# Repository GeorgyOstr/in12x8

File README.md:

# Yet another nixie display RTC project.

### Overview
Wanted to desing esp32 powered control board usable for multiple different 8 tubes clock.
Want to make 3 iterations of clocks.

Will try to code in platformio.

Case: glass lid, 3d print support, metal exterior.
Single Type-C connector.

Based on Tom Titor design.

### Target for v1
PCB design in EAGLE. Fusion for case.
All caps MLCC.

1. Display board 
    * 2 layers
    * Minimal footprint
    * SMD only
    * Circuitry on one side (tubes on opposite)
    * HV path minimized
    * 8 tubes IN12
    * [HV552](https://ww1.microchip.com/downloads/en/DeviceDoc/HV5523-32-Channel-Serial-to-Parallel-Converter-with-Open-Drain-Outputs-Data-Sheet-20005700A.pdf)
    
    * optional: custom HV supply onboard
    
2. Control board (beta)
    * 2 layers
    * Modules usage
    * Same footprint as display
    * Circuitry on one side
    * ESP32
    * [DS3232](https://www.analog.com/media/en/technical-documentation/data-sheets/ds3232.pdf)
    * [Taylor Electronics HVPS 1364](https://www.shop-tes.com/content/Datasheets/8002K.pdf)
    * [Potentiometer](https://www.mouser.jp/datasheet/2/609/MAX5460_MAX5468-3129691.pdf)
    * [Type C](https://www.mouser.jp/ProductDetail/Wurth-Elektronik/632723300021?qs=t3bE0qb%2FqEJYzZ4bEQN6Ug%3D%3D)
    * Full control on HV 

    * optional: battery support

### Target for v2

2. Control board
    * 2 layers
    * Minimal footprint
    * SMD only except USB-c
    * No modules
    * Battery support

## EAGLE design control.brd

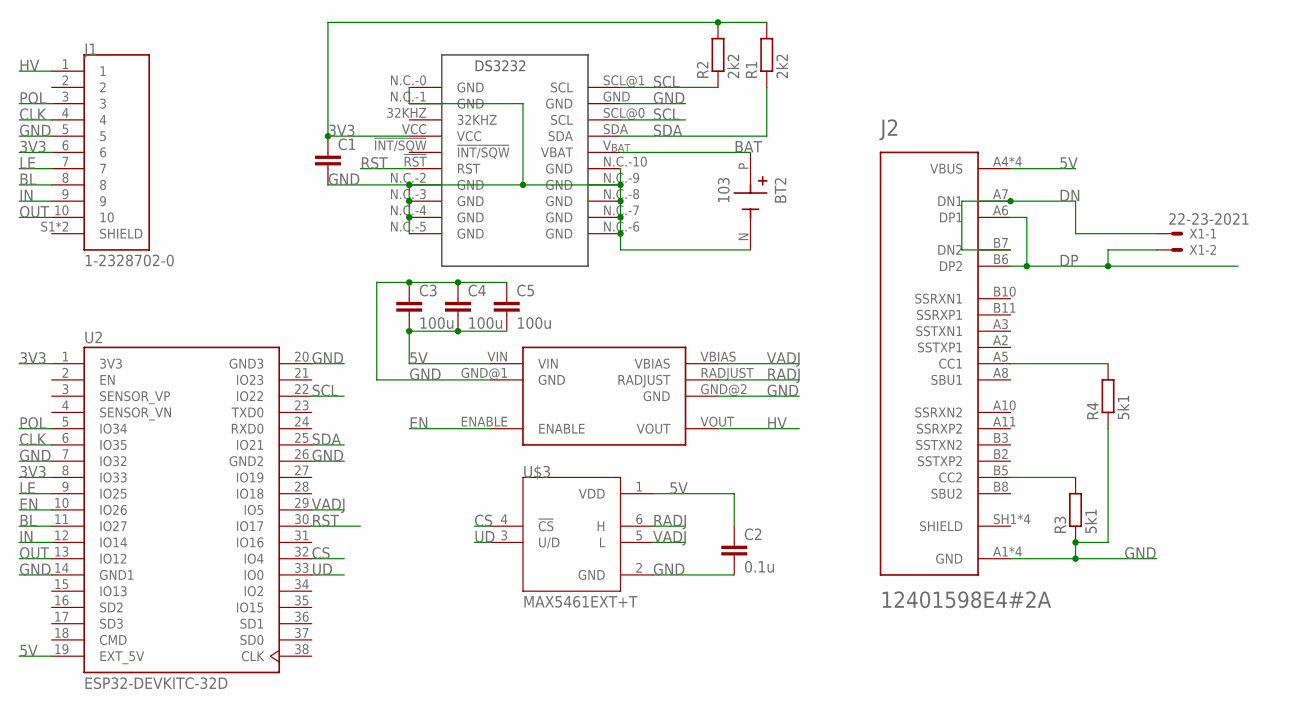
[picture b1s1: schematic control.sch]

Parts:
BT2: 103; BAT_103
C1: C-EUC0805; C0805
C2: 0.1u; C0805
C3, C4, C5: 100u; C1210
J1: 1-2328702-0; TE_1-2328702-0
J2: 12401598E4#2A; AMPHENOL_12401598E4#2A
R1, R2: 2k2; R0805
R3, R4: 5k1; R0805
U2: ESP32-DEVKITC-32D; MODULE_ESP32-DEVKITC-32D
U$1: DS3232; SO20-2
U$2: HV_PSU
U$3: MAX5461EXT+T; SOT65P210X110-6N
X1: 22-23-2021

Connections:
3V3: C1.1, J1.6, R1.2, R2.2, U2.1 (3V3), U2.8 (IO33), U$1.VCC
5V: C2.1, C3.2, C4.2, C5.2, J2.A4 (VBUS), J2.A9 (VBUS), J2.B4 (VBUS), J2.B9 (VBUS), U2.19 (EXT_5V), U$2.VIN, U$3.1 (VDD)
BAT: BT2.P (POS), U$1.V_{BAT} (VBAT)
BL: J1.8, U2.11 (IO27)
CLK: J1.4, U2.6 (IO35)
CS: U2.32 (IO4), U$3.4 (!CS)
DN: J2.A7 (DN1), J2.B7 (DN2), X1.1
DP: J2.A6 (DP1), J2.B6 (DP2), X1.2
EN: U2.10 (IO26), U$2.ENABLE
GND: BT2.N (NEG), C1.2, C2.2, C3.1, C4.1, C5.1, J1.5, J2.A1 (GND), J2.A12 (GND), J2.B1 (GND), J2.B12 (GND), R3.1, R4.1, U2.7 (IO32), U2.14 (GND1), U2.20 (GND3), U2.26 (GND2), U$1.GND, U$1.N.C.-0 (GND), U$1.N.C.-1 (GND), U$1.N.C.-2 (GND), U$1.N.C.-3 (GND), U$1.N.C.-4 (GND), U$1.N.C.-5 (GND), U$1.N.C.-6 (GND), U$1.N.C.-7 (GND), U$1.N.C.-8 (GND), U$1.N.C.-9 (GND), U$1.N.C.-10 (GND), U$2.GND@1 (GND), U$2.GND@2 (GND), U$3.2 (GND)
HV: J1.1, U$2.VOUT
IN: J1.9, U2.12 (IO14)
LE: J1.7, U2.9 (IO25)
unnamed: J2.B5 (CC2), R3.2
unnamed: J2.A5 (CC1), R4.2
OUT: J1.10, U2.13 (IO12)
POL: J1.3, U2.5 (IO34)
RADJ: U$2.RADJUST, U$3.6 (H)
RST: U2.30 (IO17), U$1.!RST (RST)
SCL: R2.1, U2.22 (IO22), U$1.SCL@0 (SCL), U$1.SCL@1 (SCL)
SDA: R1.1, U2.25 (IO21), U$1.SDA
SHIELD: J2.SH1 (SHIELD), J2.SH2 (SHIELD), J2.SH3 (SHIELD), J2.SH4 (SHIELD)
UD: U2.33 (IO0), U$3.3 (U/D)
VADJ: U2.29 (IO5), U$2.VBIAS, U$3.5 (L)

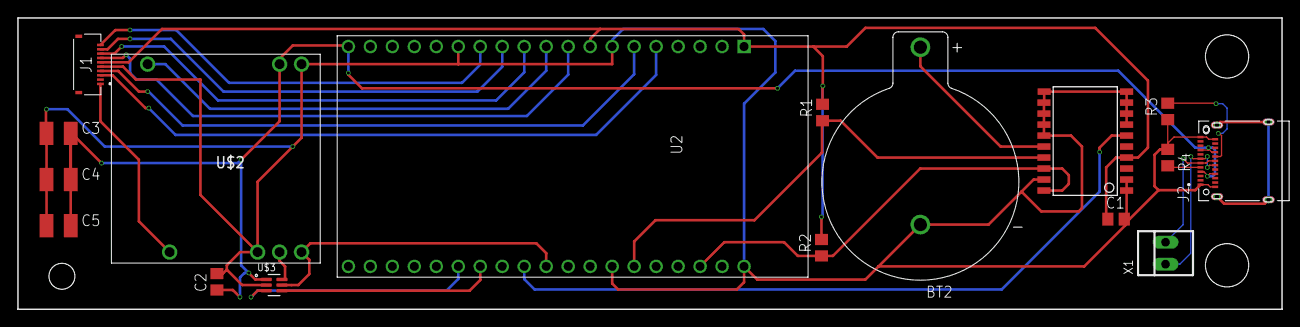
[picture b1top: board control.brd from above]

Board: 2 copper layers, 146.1 x 33.7 mm, 17 parts (0 on the bottom side), 24 nets.

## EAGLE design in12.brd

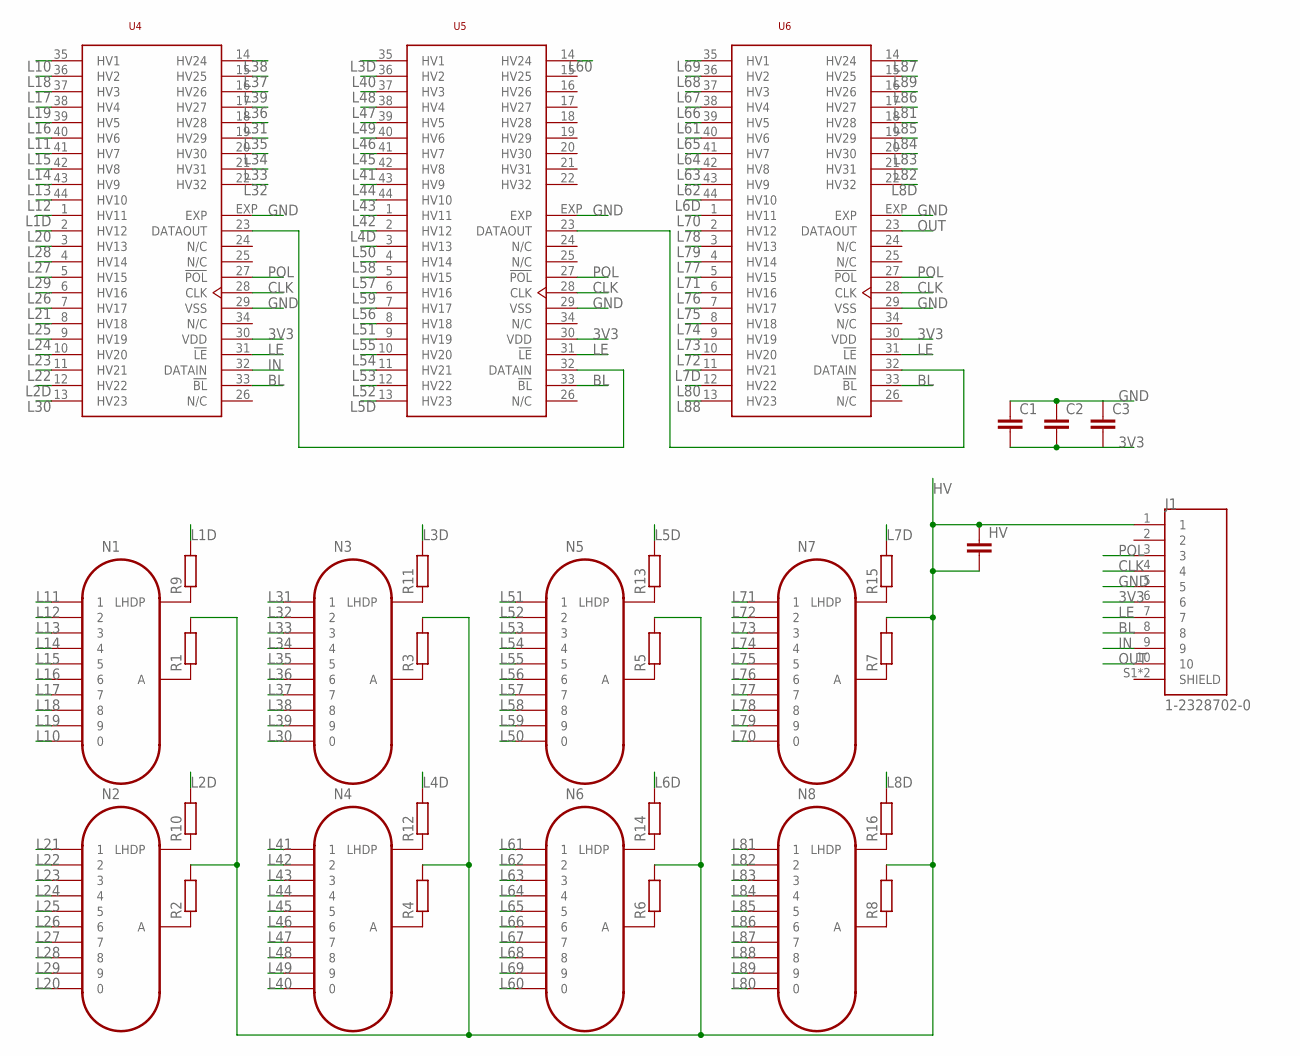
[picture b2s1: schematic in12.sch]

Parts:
C1, C2, C3: C-EUC0805; C0805
HV: C-EUC1206; C1206
J1: 1-2328702-0; TE_1-2328702-0
N1, N2, N3, N4, N5, N6, N7, N8: IN-12B; IN-12
R1, R2, R3, R4, R5, R6, R7, R8: R-EU_R1206; R1206
R9, R10, R11, R12, R13, R14, R15, R16: R-EU_R0805; R0805
U4, U5, U6: HV5523; QFN-44-7X7

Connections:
3V3: C1.2, C2.2, C3.2, J1.6, U4.30 (VDD), U5.30 (VDD), U6.30 (VDD)
BL: J1.8, U4.33 (!BL), U5.33 (!BL), U6.33 (!BL)
CLK: J1.4, U4.28 (CLK), U5.28 (CLK), U6.28 (CLK)
GND: C1.1, C2.1, C3.1, J1.5, U4.29 (VSS), U4.EXP, U5.29 (VSS), U5.EXP, U6.29 (VSS), U6.EXP
HV: HV.1, HV.2, J1.1, R1.2, R2.2, R3.2, R4.2, R5.2, R6.2, R7.2, R8.2
IN: J1.9, U4.32 (DATAIN)
L1D: R9.2, U4.1 (HV11)
L2D: R10.2, U4.12 (HV22)
L3D: R11.2, U5.35 (HV1)
L4D: R12.2, U5.2 (HV12)
L5D: R13.2, U5.13 (HV23)
L6D: R14.2, U6.44 (HV10)
L7D: R15.2, U6.11 (HV21)
L8D: R16.2, U6.22 (HV32)
L10: N1.0, U4.35 (HV1)
L11: N1.1, U4.40 (HV6)
L12: N1.2, U4.44 (HV10)
L13: N1.3, U4.43 (HV9)
L14: N1.4, U4.42 (HV8)
L15: N1.5, U4.41 (HV7)
L16: N1.6, U4.39 (HV5)
L17: N1.7, U4.37 (HV3)
L18: N1.8, U4.36 (HV2)
L19: N1.9, U4.38 (HV4)
L20: N2.0, U4.2 (HV12)
L21: N2.1, U4.7 (HV17)
L22: N2.2, U4.11 (HV21)
L23: N2.3, U4.10 (HV20)
L24: N2.4, U4.9 (HV19)
L25: N2.5, U4.8 (HV18)
L26: N2.6, U4.6 (HV16)
L27: N2.7, U4.4 (HV14)
L28: N2.8, U4.3 (HV13)
L29: N2.9, U4.5 (HV15)
L30: N3.0, U4.13 (HV23)
L31: N3.1, U4.18 (HV28)
L32: N3.2, U4.22 (HV32)
L33: N3.3, U4.21 (HV31)
L34: N3.4, U4.20 (HV30)
L35: N3.5, U4.19 (HV29)
L36: N3.6, U4.17 (HV27)
L37: N3.7, U4.15 (HV25)
L38: N3.8, U4.14 (HV24)
L39: N3.9, U4.16 (HV26)
L40: N4.0, U5.36 (HV2)
L41: N4.1, U5.42 (HV8)
L42: N4.2, U5.1 (HV11)
L43: N4.3, U5.44 (HV10)
L44: N4.4, U5.43 (HV9)
L45: N4.5, U5.41 (HV7)
L46: N4.6, U5.40 (HV6)
L47: N4.7, U5.38 (HV4)
L48: N4.8, U5.37 (HV3)
L49: N4.9, U5.39 (HV5)
L50: N5.0, U5.3 (HV13)
L51: N5.1, U5.8 (HV18)
L52: N5.2, U5.12 (HV22)
L53: N5.3, U5.11 (HV21)
L54: N5.4, U5.10 (HV20)
L55: N5.5, U5.9 (HV19)
L56: N5.6, U5.7 (HV17)
L57: N5.7, U5.5 (HV15)
L58: N5.8, U5.4 (HV14)
L59: N5.9, U5.6 (HV16)
L60: N6.0, U5.14 (HV24)
L61: N6.1, U6.39 (HV5)
L62: N6.2, U6.43 (HV9)
L63: N6.3, U6.42 (HV8)
L64: N6.4, U6.41 (HV7)
L65: N6.5, U6.40 (HV6)
L66: N6.6, U6.38 (HV4)
L67: N6.7, U6.37 (HV3)
L68: N6.8, U6.36 (HV2)
L69: N6.9, U6.35 (HV1)
L70: N7.0, U6.1 (HV11)
L71: N7.1, U6.5 (HV15)
L72: N7.2, U6.10 (HV20)
L73: N7.3, U6.9 (HV19)
L74: N7.4, U6.8 (HV18)
L75: N7.5, U6.7 (HV17)
L76: N7.6, U6.6 (HV16)
L77: N7.7, U6.4 (HV14)
L78: N7.8, U6.2 (HV12)
L79: N7.9, U6.3 (HV13)
L80: N8.0, U6.12 (HV22)
L81: N8.1, U6.17 (HV27)
L82: N8.2, U6.21 (HV31)
L83: N8.3, U6.20 (HV30)
L84: N8.4, U6.19 (HV29)
L85: N8.5, U6.18 (HV28)
L86: N8.6, U6.16 (HV26)
L87: N8.7, U6.14 (HV24)
L88: N8.8, U6.13 (HV23)
L89: N8.9, U6.15 (HV25)
LE: J1.7, U4.31 (!LE), U5.31 (!LE), U6.31 (!LE)
unnamed: N1.A, R1.1
unnamed: N2.A, R2.1
unnamed: N3.A, R3.1
unnamed: N4.A, R4.1
unnamed: N5.A, R5.1
unnamed: N6.A, R6.1
unnamed: N7.A, R7.1
unnamed: N8.A, R8.1
unnamed: N1.LHDP, R9.1
unnamed: N2.LHDP, R10.1
unnamed: N3.LHDP, R11.1
unnamed: N4.LHDP, R12.1
unnamed: N5.LHDP, R13.1
unnamed: N6.LHDP, R14.1
unnamed: N7.LHDP, R15.1
unnamed: N8.LHDP, R16.1
unnamed: U4.23 (DATAOUT), U5.32 (DATAIN)
unnamed: U5.23 (DATAOUT), U6.32 (DATAIN)
OUT: J1.10, U6.23 (DATAOUT)
POL: J1.3, U4.27 (!POL), U5.27 (!POL), U6.27 (!POL)

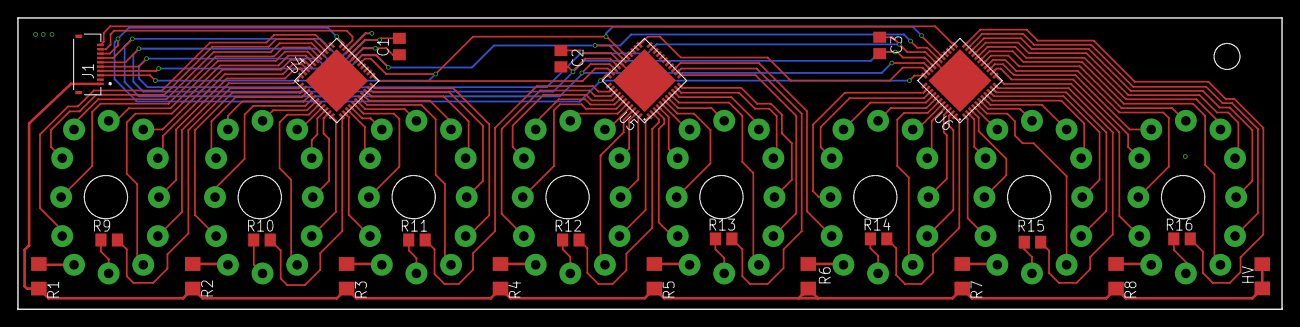
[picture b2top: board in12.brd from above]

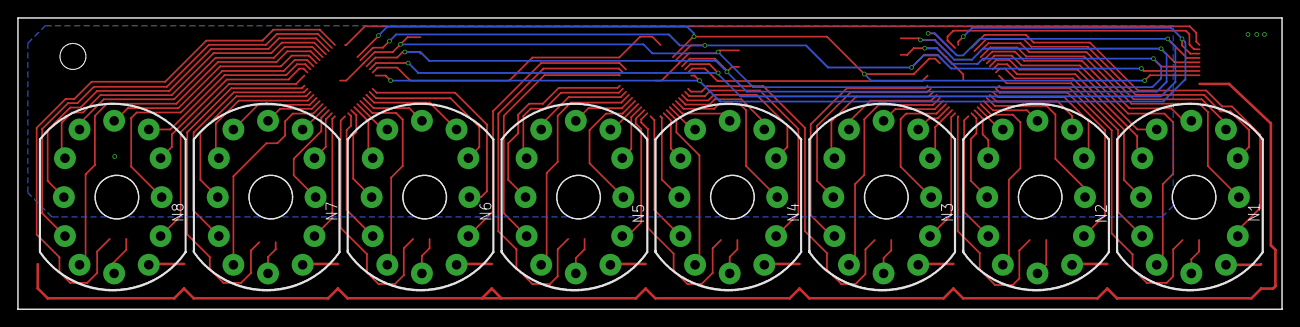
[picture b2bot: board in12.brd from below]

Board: 2 copper layers, 146.1 x 33.7 mm, 32 parts (8 on the bottom side), 115 nets.

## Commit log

2024-01-10 initcomm
2024-01-10 5523 still need shuffle pins
2024-01-12 hv single layer routed
2024-01-12 compact
2024-01-12 added m.2 connector
2024-01-14 control board, adapter ffc wire
2024-01-15 routing connector
2024-01-15 lamp board finished, working on control
2024-01-20 add readme, brushup board
2024-01-20 added potentio, readme update
2024-01-21 reg update
2024-01-21 Found wurth typec
2024-04-19 started ratsnest, finished usb-c viring
